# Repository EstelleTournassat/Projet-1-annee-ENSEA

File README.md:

## Projet-1-année-ENSEA

Projet de télémetrie en lien avec le projet CoHoMa.

# Description :
Les communications entre un robot et son téléopérateur utilisent un réseau wifi maillé (mesh 802.11s). Bien que très robuste, la portée de ce réseau n’est pas infinie (maximum 50m par balise), et une perte de connexion peut survenir même à plus faible distance, notamment à cause du relief ou de la végétation.
L’objectif est donc de mettre en place un réseau secondaire, de plus forte portée mais de débit réduit, permettant d’assurer:

-> la continuité de la téléopération du robot en cas de perte de la liaison wifi  
-> l’arrêt d’urgence des moteurs a la demande ou en cas de perte totale de connexion  
-> la remontée de la position GPS du robot (télémetrie)  
-> Le tout pourra être opéré sur batterie.  

Ce réseau secondaire va utiliser les composants NRF24L01 de Nordic Semiconductor, et devra faire communiquer des STM32 et des cartes de type Raspberry pi zero.

# Objectifs :
-> mise en œuvre du réseau nrf24  
-> réalisation du module autonome: batterie, boitier, PCB  
-> conception de l’arrêt d’urgence et du télépilotage et intégration du GPS  

# Les délais :
-> 17/04 : GANTT (format excel) + spécifications techniques/diagramme d’architecture (format pdf)  
-> 09/05 : Auto-évaluation des compétences  
-> 06/06 : Livrable final et Soutenance finale  

# Les tâches principales:
-> Réaliser de deux PCB (1 pour la STM32 et le module NRF24, 1 pour la raspberry pi et le module NRF24)

-> Faire communiquer deux STM32 entre elles

-> Faire communiquer deux Raspberry pi entre elles 

# Répartition des tâches :
Cf GANTT 

# Description documents du repository :
-> "datasheet_NRF24L01.PDF" : Datasheet complète du module NRF24 utilisé

-> "datasheet_NUCLEOL412KB" : Datasheet complète de la carte NUCLEOL412KB utilisée (STM32)

-> "boutonstop.cpp" : code Bouton Stop pour la raspberry pi 

-> "GANTT.md" : GANTT prévisionnel et GANTT réel

-> "Codes_Communication.STM32.md" : codes communication et fiches PIN de la STM32 et du NRF24

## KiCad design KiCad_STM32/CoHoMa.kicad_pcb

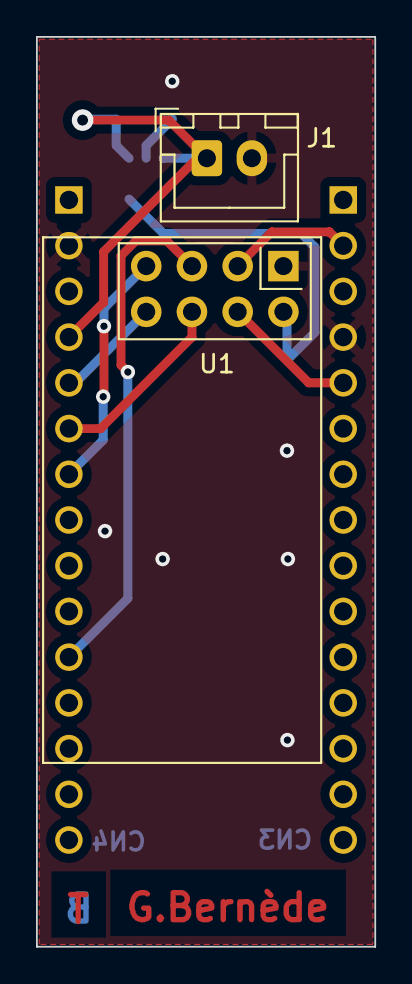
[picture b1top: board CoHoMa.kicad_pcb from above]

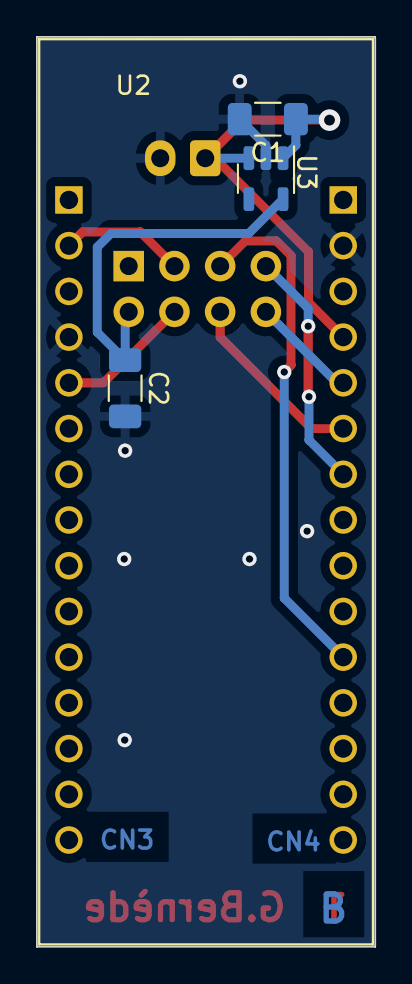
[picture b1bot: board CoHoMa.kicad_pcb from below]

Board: 2 copper layers, 18.8 x 50.5 mm, 6 parts (4 on the bottom side), 9 nets.

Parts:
C1, C2: 1uF; C_1206_3216Metric_Pad1.33x1.80mm_HandSolder
J1: INPUT; JST_XH_B2B-XH-A_1x02_P2.50mm_Vertical
U1: NRF24L01_Breakout; nRF24L01_Breakout
U2: STM32L412KBTx; MODULE_NUCLEO-L412KB
U3: BU33SD5WG-TR; SOT-23-5

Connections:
+3.3V: C2.1, U1.2 (VCC), U3.5 (VOUT)
+5V: C1.1, J1.1, U2.5 (VDDA), U3.1 (VIN), U3.3 (~SHDN)
CE: U1.3 (CE), U2.20 (PA10)
CSN: U1.4 (~CSN), U2.22 (PA12)
GND: C1.2, C2.2, J1.2, U1.1 (GND), U2.16 (VSS), U3.2 (GND)
IRQ: U1.8 (IRQ), U2.8 (PA2)
MISO: U1.7 (MISO), U2.12 (PA6)
MOSI: U1.6 (MOSI), U2.13 (PA7)
SCK: U1.5 (SCK), U2.7 (PA1)

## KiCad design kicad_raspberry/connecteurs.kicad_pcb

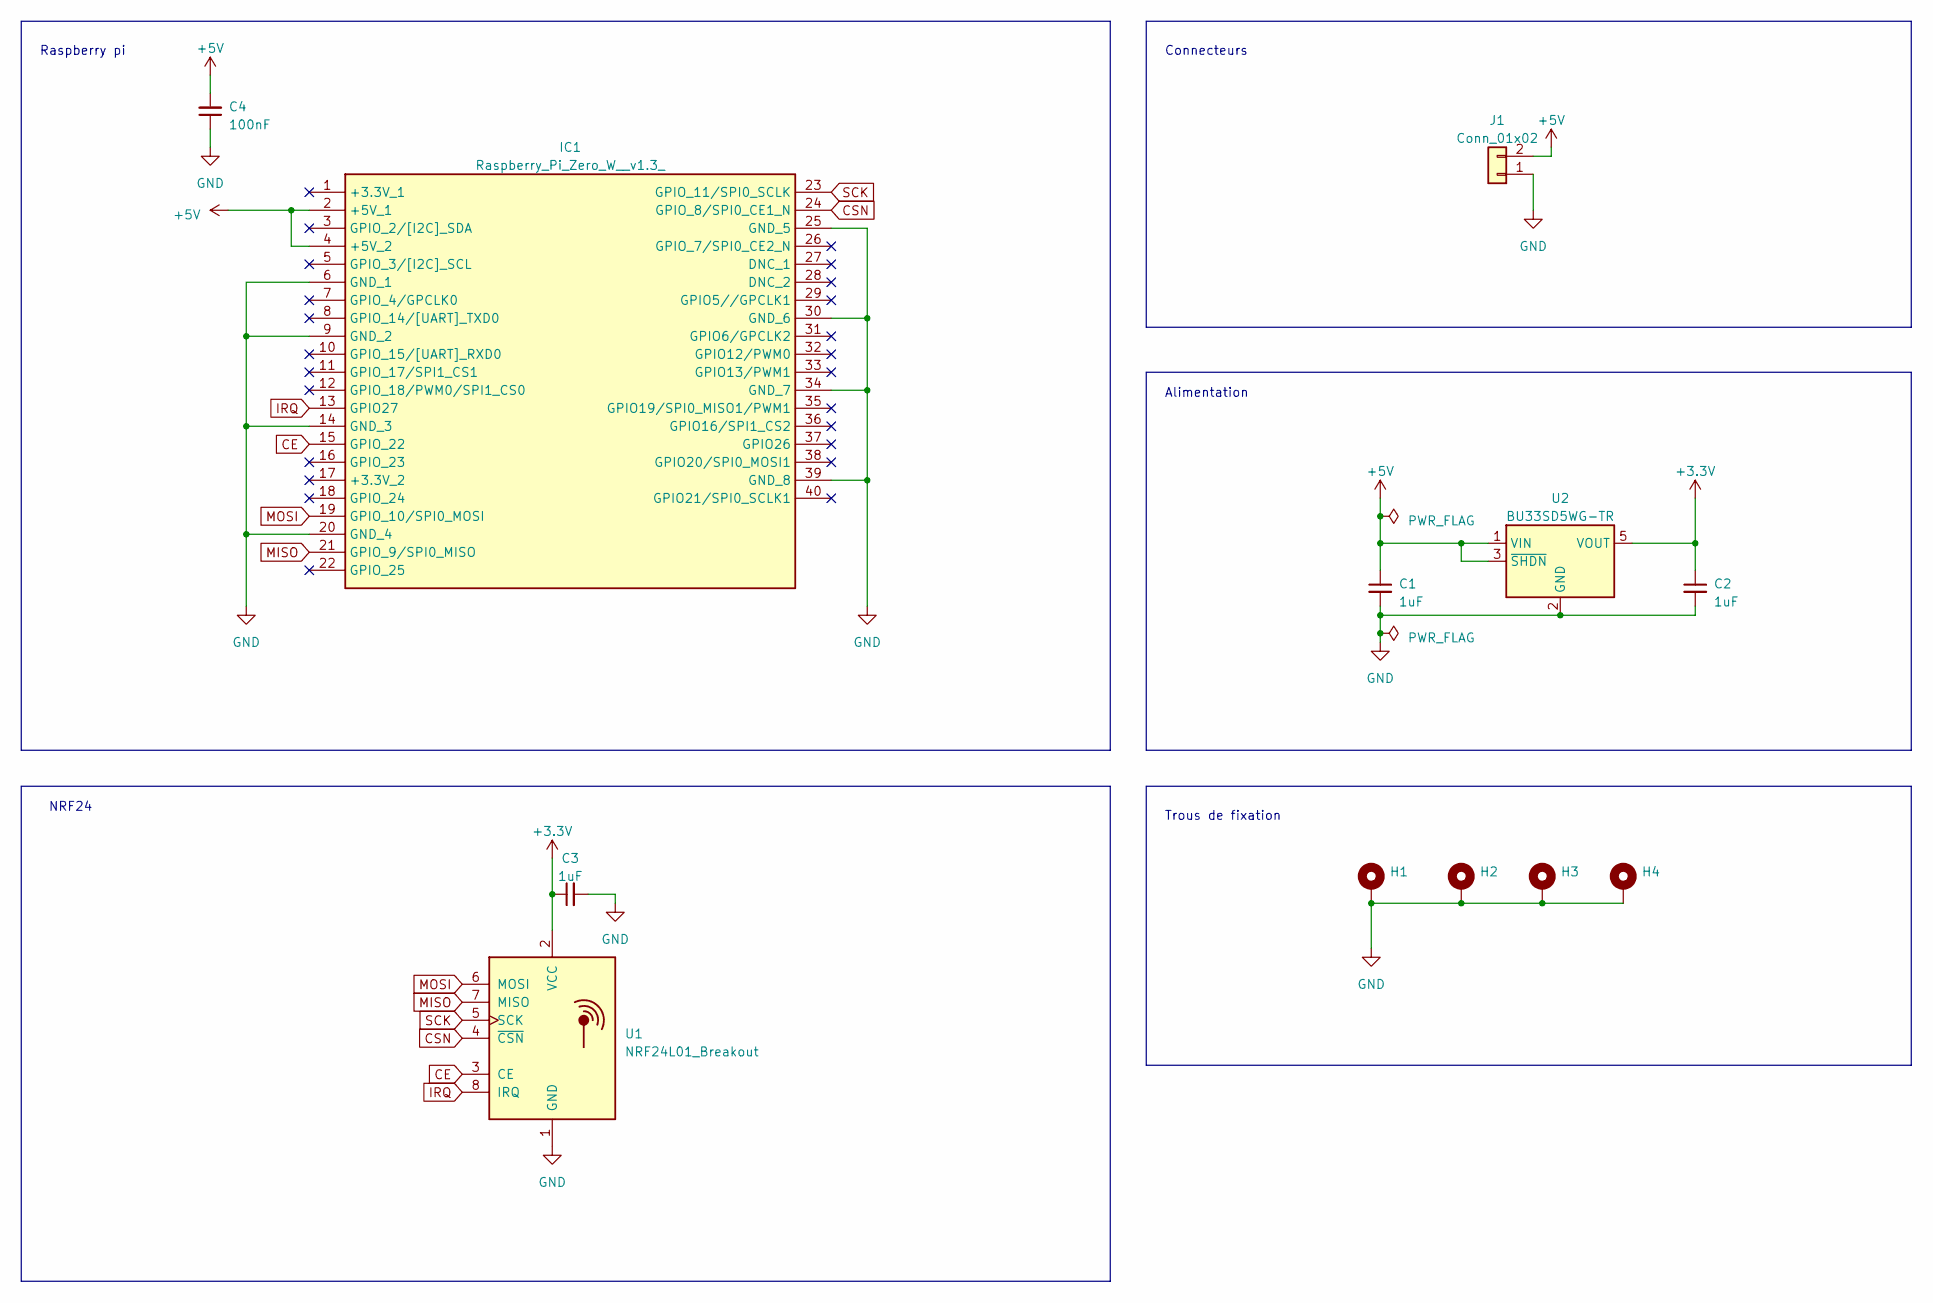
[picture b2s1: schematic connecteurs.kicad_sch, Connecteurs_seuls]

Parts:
C1, C2, C3: 1uF; C_1206_3216Metric_Pad1.33x1.80mm_HandSolder
C4: 100nF; C_1206_3216Metric_Pad1.33x1.80mm_HandSolder
H1, H2, H3, H4: MountingHole_Pad; MountingHole_2.7mm_M2.5_DIN965_Pad
IC1: Raspberry_Pi_Zero_W__v1.3_; PinHeader_2x20_P2.54mm_Vertical; Manufacturer_Part_Number Raspberry Pi Zero W (v1.3)
J1: Conn_01x02; JST_XH_B2B-XH-A_1x02_P2.50mm_Vertical
U1: NRF24L01_Breakout; nRF24L01_Breakout
U2: BU33SD5WG-TR; SOT-23-5

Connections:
+3.3V: C2.1, C3.1, U1.2 (VCC), U2.5 (VOUT)
+5V: C1.1, C4.2, IC1.2 (+5V_1), IC1.4 (+5V_2), J1.2, U2.1 (VIN), U2.3 (~SHDN)
CE: IC1.15 (GPIO_22), U1.3 (CE)
CSN: IC1.24 (GPIO_8/SPI0_CE1_N), U1.4 (~CSN)
GND: C1.2, C2.2, C3.2, C4.1, H1.1, H2.1, H3.1, H4.1, IC1.6 (GND_1), IC1.9 (GND_2), IC1.14 (GND_3), IC1.20 (GND_4), IC1.25 (GND_5), IC1.30 (GND_6), IC1.34 (GND_7), IC1.39 (GND_8), J1.1, U1.1 (GND), U2.2 (GND)
IRQ: IC1.13 (GPIO27), U1.8 (IRQ)
MISO: IC1.21 (GPIO_9/SPI0_MISO), U1.7 (MISO)
MOSI: IC1.19 (GPIO_10/SPI0_MOSI), U1.6 (MOSI)
SCK: IC1.23 (GPIO_11/SPI0_SCLK), U1.5 (SCK)

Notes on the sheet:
Trous de fixation
Connecteurs
NRF24
Raspberry pi
Alimentation

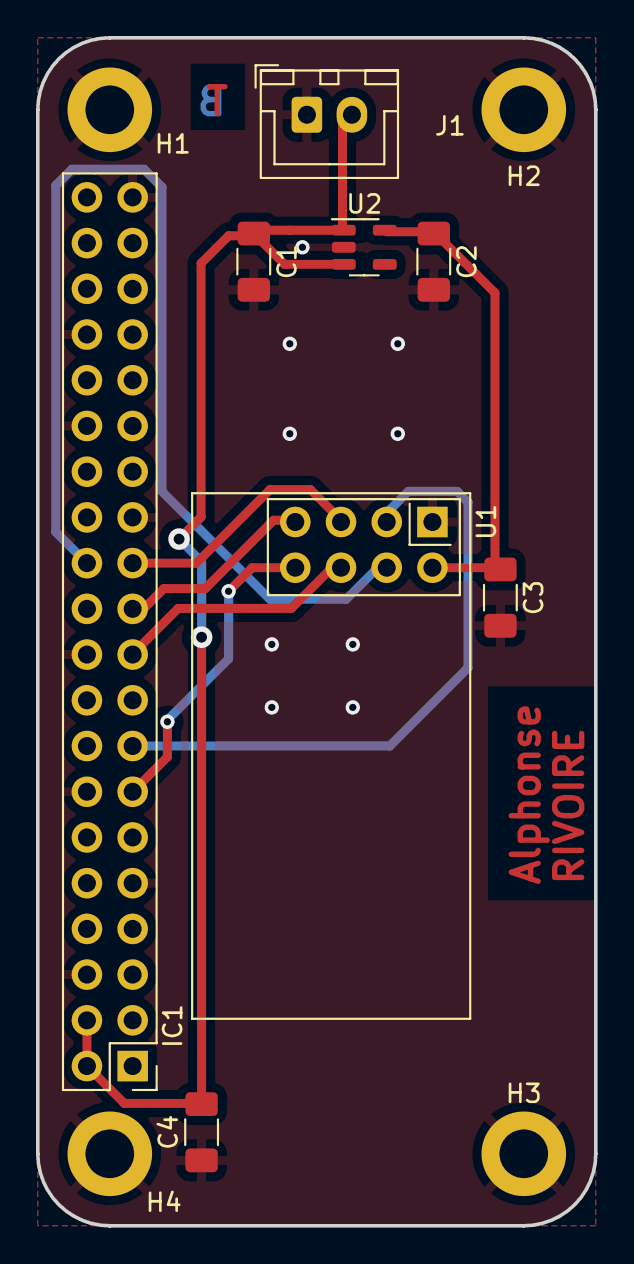
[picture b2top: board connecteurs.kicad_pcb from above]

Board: 2 copper layers, 31.0 x 66.0 mm, 12 parts (0 on the bottom side), 9 nets.

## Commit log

2023-04-06 Create Notes
2023-04-06 Create Références
2023-04-06 Update Notes
2023-04-06 Update Références
2023-04-13 Rename Références to Références.md
2023-04-13 Rename Notes to Notes.md
2023-04-13 Create Code, librairie STM32
2023-04-13 Update Code, librairie STM32
2023-06-05 Rename Références.md to ressources_utiles.md
2023-06-05 GANTT.md
2023-06-05 Rename Codes.STM32.md to Codes_Communication.STM32.md
2023-06-05 Rename MY_NRF24.c to Codes_Communication.STM32/MY_NRF24.c
2023-06-05 Rename MY_NRF24.h to Codes_Communication.STM32/MY_NRF24.h
2023-06-05 Rename main_RX.c to Codes_Communication.STM32/main_RX.c
2023-06-05 Rename main_TX.c to Codes_Communication.STM32/main_TX.c
2023-06-05 Rename nRF24L01.h to Codes_Communication.STM32/nRF24L01.h
2023-06-05 Create DATASHEET
2023-06-05 Rename Montage.STM32 to Montage.STM32.md
2023-06-05 Create Montage_STM32_NRF24
